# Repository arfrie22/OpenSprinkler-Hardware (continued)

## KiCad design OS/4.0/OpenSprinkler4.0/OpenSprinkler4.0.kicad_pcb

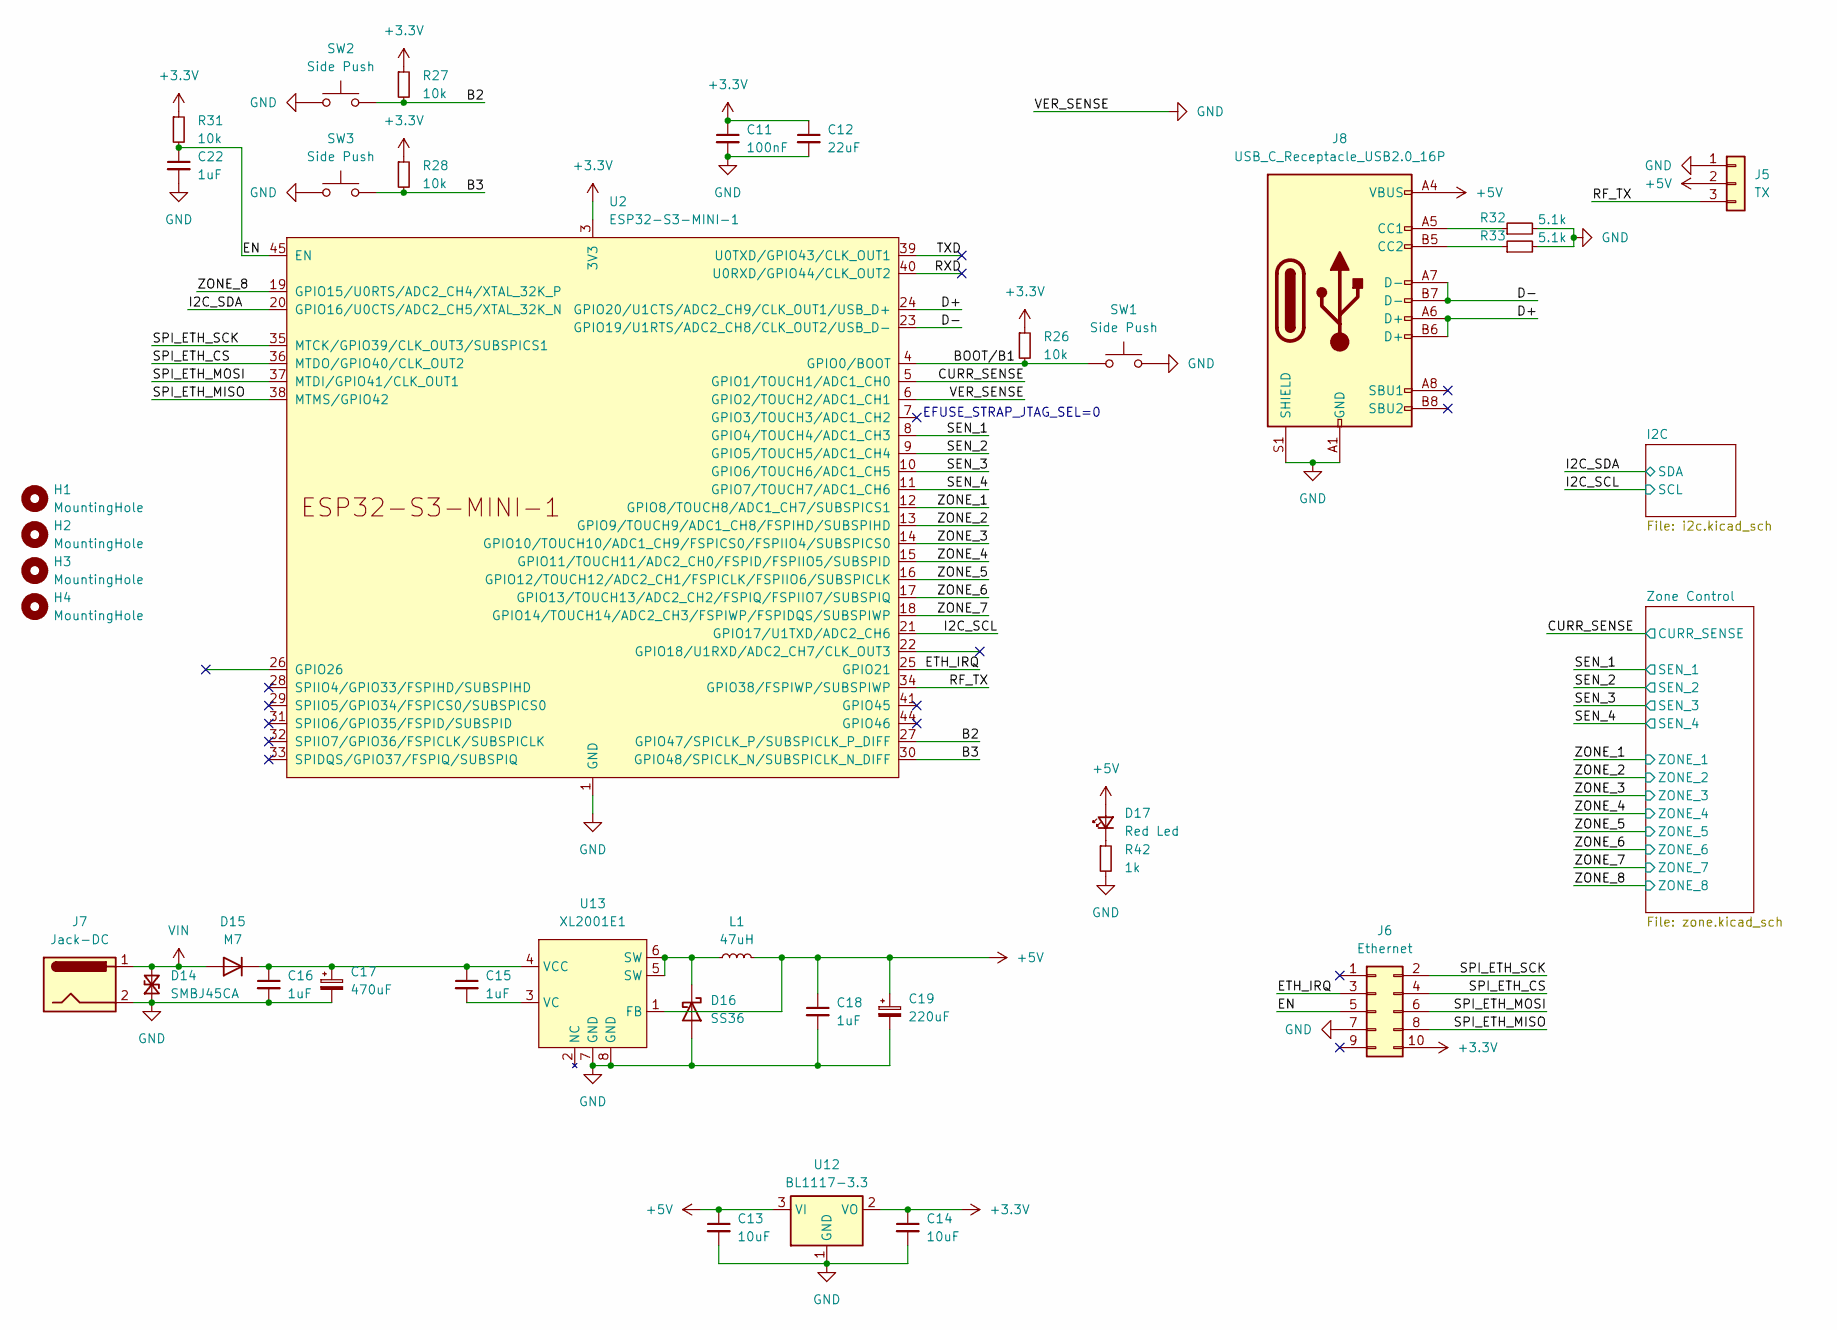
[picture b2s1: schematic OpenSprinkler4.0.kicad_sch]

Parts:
C11: 100nF; C_0603_1608Metric_Pad1.08x0.95mm_HandSolder; JLCPCB Part # C14663
C12: 22uF; C_0805_2012Metric_Pad1.18x1.45mm_HandSolder; JLCPCB Part # C45783
C13, C14: 10uF; C_0603_1608Metric_Pad1.08x0.95mm_HandSolder; JLCPCB Part # C96446
C15, C16, C18, C22: 1uF; C_0603_1608Metric_Pad1.08x0.95mm_HandSolder; JLCPCB Part # C15849
C17: 470uF; CP_Radial_L20.0mm_D10.0mm_P5.00mm_Horizontal; JLCPCB Part # C2760863
C19: 220uF; CP_Radial_L12.0mm_D8.0mm_P3.50mm_Horizontal; JLCPCB Part # C2831783
D14: SMBJ45CA; D_SMB; JLCPCB Part # C7466424
D15: M7; D_SMA; JLCPCB Part # C7420350
D16: SS36; D_SMA; JLCPCB Part # C7420367
D17: Red Led; LED_0603_1608Metric_Pad1.05x0.95mm_HandSolder; JLCPCB Part # C2286
H1, H2, H3, H4: MountingHole; MountingHole_5.6mm; JLCPCB Part # N/A
J5: TX; PinSocket_1x03_P2.54mm_Horizontal; Part Number 1-0301FBV0T; JLCPCB Part # C2935993
J6: Ethernet; IDC-Header_2x05_P2.54mm_Horizontal; JLCPCB Part # C9140
J7: Jack-DC; BarrelJack_Horizontal; JLCPCB Part # C3010533
J8: USB_C_Receptacle_USB2.0_16P; USB_C_Receptacle_HRO_TYPE-C-31-M-12; JLCPCB Part # C2927038
L1: 47uH; L_Sunlord_MWSA1004S; JLCPCB Part # C182153
R26, R27, R28, R31: 10k; R_0603_1608Metric_Pad0.98x0.95mm_HandSolder; JLCPCB Part # C25804
R32, R33: 5.1k; R_0603_1608Metric_Pad0.98x0.95mm_HandSolder; JLCPCB Part # C23186
R42: 1k; R_0603_1608Metric_Pad0.98x0.95mm_HandSolder; JLCPCB Part # C21190
SW1, SW2, SW3: Side Push; SW_Tactile_SPST_Angled_PTS645Vx83-2LFS; JLCPCB Part # C493059
U2: ESP32-S3-MINI-1; JLCPCB Part # C2913206
U12: BL1117-3.3; SOT-223-3_TabPin2; JLCPCB Part # C5400
U13: XL2001E1; SOP-8_3.9x4.9mm_P1.27mm; JLCPCB Part # C73336

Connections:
+3.3V: C11.1, C12.1, C14.1, J6.10, R26.1, R27.1, R28.1, R31.1, U2.3 (3V3), U12.2 (VO); also elsewhere on the board
+5V: C13.1, C18.1, C19.1, D17.2 (A), J5.2, J8.A4 (VBUS), J8.A9 (VBUS), J8.B4 (VBUS), J8.B9 (VBUS), L1.2, U12.3 (VI), U13.1 (FB); also elsewhere on the board
/B2: R27.2, SW2.1, U2.27 (GPIO47/SPICLK_P/SUBSPICLK_P_DIFF)
/B3: R28.2, SW3.1, U2.30 (GPIO48/SPICLK_N/SUBSPICLK_N_DIFF)
/BOOT/B1: R26.2, SW1.1, U2.4 (GPIO0/BOOT)
/CURR_SENSE: U2.5 (GPIO1/TOUCH1/ADC1_CH0); also elsewhere on the board
/D+: J8.A6 (D+), J8.B6 (D+), U2.24 (GPIO20/U1CTS/ADC2_CH9/CLK_OUT1/USB_D+)
/D-: J8.A7 (D-), J8.B7 (D-), U2.23 (GPIO19/U1RTS/ADC2_CH8/CLK_OUT2/USB_D-)
/EN: C22.1, J6.5, R31.2, U2.45 (EN)
/ETH_IRQ: J6.3, U2.25 (GPIO21)
/I2C_SCL: U2.21 (GPIO17/U1TXD/ADC2_CH6); also elsewhere on the board
/I2C_SDA: U2.20 (GPIO16/U0CTS/ADC2_CH5/XTAL_32K_N); also elsewhere on the board
/RF_TX: J5.3, U2.34 (GPIO38/FSPIWP/SUBSPIWP)
/RXD: U2.40 (U0RXD/GPIO44/CLK_OUT2)
/SEN_1: U2.8 (GPIO4/TOUCH4/ADC1_CH3); also elsewhere on the board
/SEN_2: U2.9 (GPIO5/TOUCH5/ADC1_CH4); also elsewhere on the board
/SEN_3: U2.10 (GPIO6/TOUCH6/ADC1_CH5); also elsewhere on the board
/SEN_4: U2.11 (GPIO7/TOUCH7/ADC1_CH6); also elsewhere on the board
/SPI_ETH_CS: J6.4, U2.36 (MTDO/GPIO40/CLK_OUT2)
/SPI_ETH_MISO: J6.8, U2.38 (MTMS/GPIO42)
/SPI_ETH_MOSI: J6.6, U2.37 (MTDI/GPIO41/CLK_OUT1)
/SPI_ETH_SCK: J6.2, U2.35 (MTCK/GPIO39/CLK_OUT3/SUBSPICS1)
/TXD: U2.39 (U0TXD/GPIO43/CLK_OUT1)
/ZONE_1: U2.12 (GPIO8/TOUCH8/ADC1_CH7/SUBSPICS1); also elsewhere on the board
/ZONE_2: U2.13 (GPIO9/TOUCH9/ADC1_CH8/FSPIHD/SUBSPIHD); also elsewhere on the board
/ZONE_3: U2.14 (GPIO10/TOUCH10/ADC1_CH9/FSPICS0/FSPIIO4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); also elsewhere on the board
/ZONE_4: U2.15 (GPIO11/TOUCH11/ADC2_CH0/FSPID/FSPIIO5/S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); also elsewhere on the board
/ZONE_5: U2.16 (GPIO12/TOUCH12/ADC2_CH1/FSPICLK/FSPIIO6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); also elsewhere on the board
/ZONE_6: U2.17 (GPIO13/TOUCH13/ADC2_CH2/FSPIQ/FSPIIO7/S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); also elsewhere on the board
/ZONE_7: U2.18 (GPIO14/TOUCH14/ADC2_CH3/FSPIWP/FSPIDQS/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); also elsewhere on the board
/ZONE_8: U2.19 (GPIO15/U0RTS/ADC2_CH4/XTAL_32K_P); also elsewhere on the board
GND: C11.2, C12.2, C13.2, C14.2, C16.2, C17.2, C18.2, C19.2, C22.2, D14.1 (A1), D16.2 (A), J5.1, J6.7, J7.2, J8.A1 (GND), J8.A12 (GND), J8.B1 (GND), J8.B12 (GND), J8.S1 (SHIELD), R32.2, R33.2, R42.2, SW1.2, SW2.2, SW3.2, U2.1 (GND), U2.2 (GND), U2.6 (GPIO2/TOUCH2/ADC1_CH1), U2.42 (GND), U2.43 (GND), U2.46 (GND), U2.47 (GND), U2.48 (GND), U2.49 (GND), U2.50 (GND), U2.51 (GND), U2.52 (GND), U2.53 (GND), U2.54 (GND), U2.55 (GND), U2.56 (GND), U2.57 (GND), U2.58 (GND), U2.59 (GND), U2.60 (GND), U2.61 (GND), U2.62 (GND), U2.63 (GND), U2.64 (GND), U2.65 (GND), U12.1 (GND), U13.7 (GND), U13.8 (GND); also elsewhere on the board
unnamed: C15.1, C16.1, C17.1, D15.1 (K), U13.4 (VCC)
unnamed: D16.1 (K), L1.1, U13.5 (SW), U13.6 (SW)
unnamed: D17.1 (K), R42.1
unnamed: J8.A5 (CC1), R32.1
unnamed: J8.B5 (CC2), R33.1
unnamed: C15.2, U13.3 (VC)
VIN: D14.2 (A2), D15.2 (A), J7.1; also elsewhere on the board

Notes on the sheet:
EFUSE_STRAP_JTAG_SEL=0

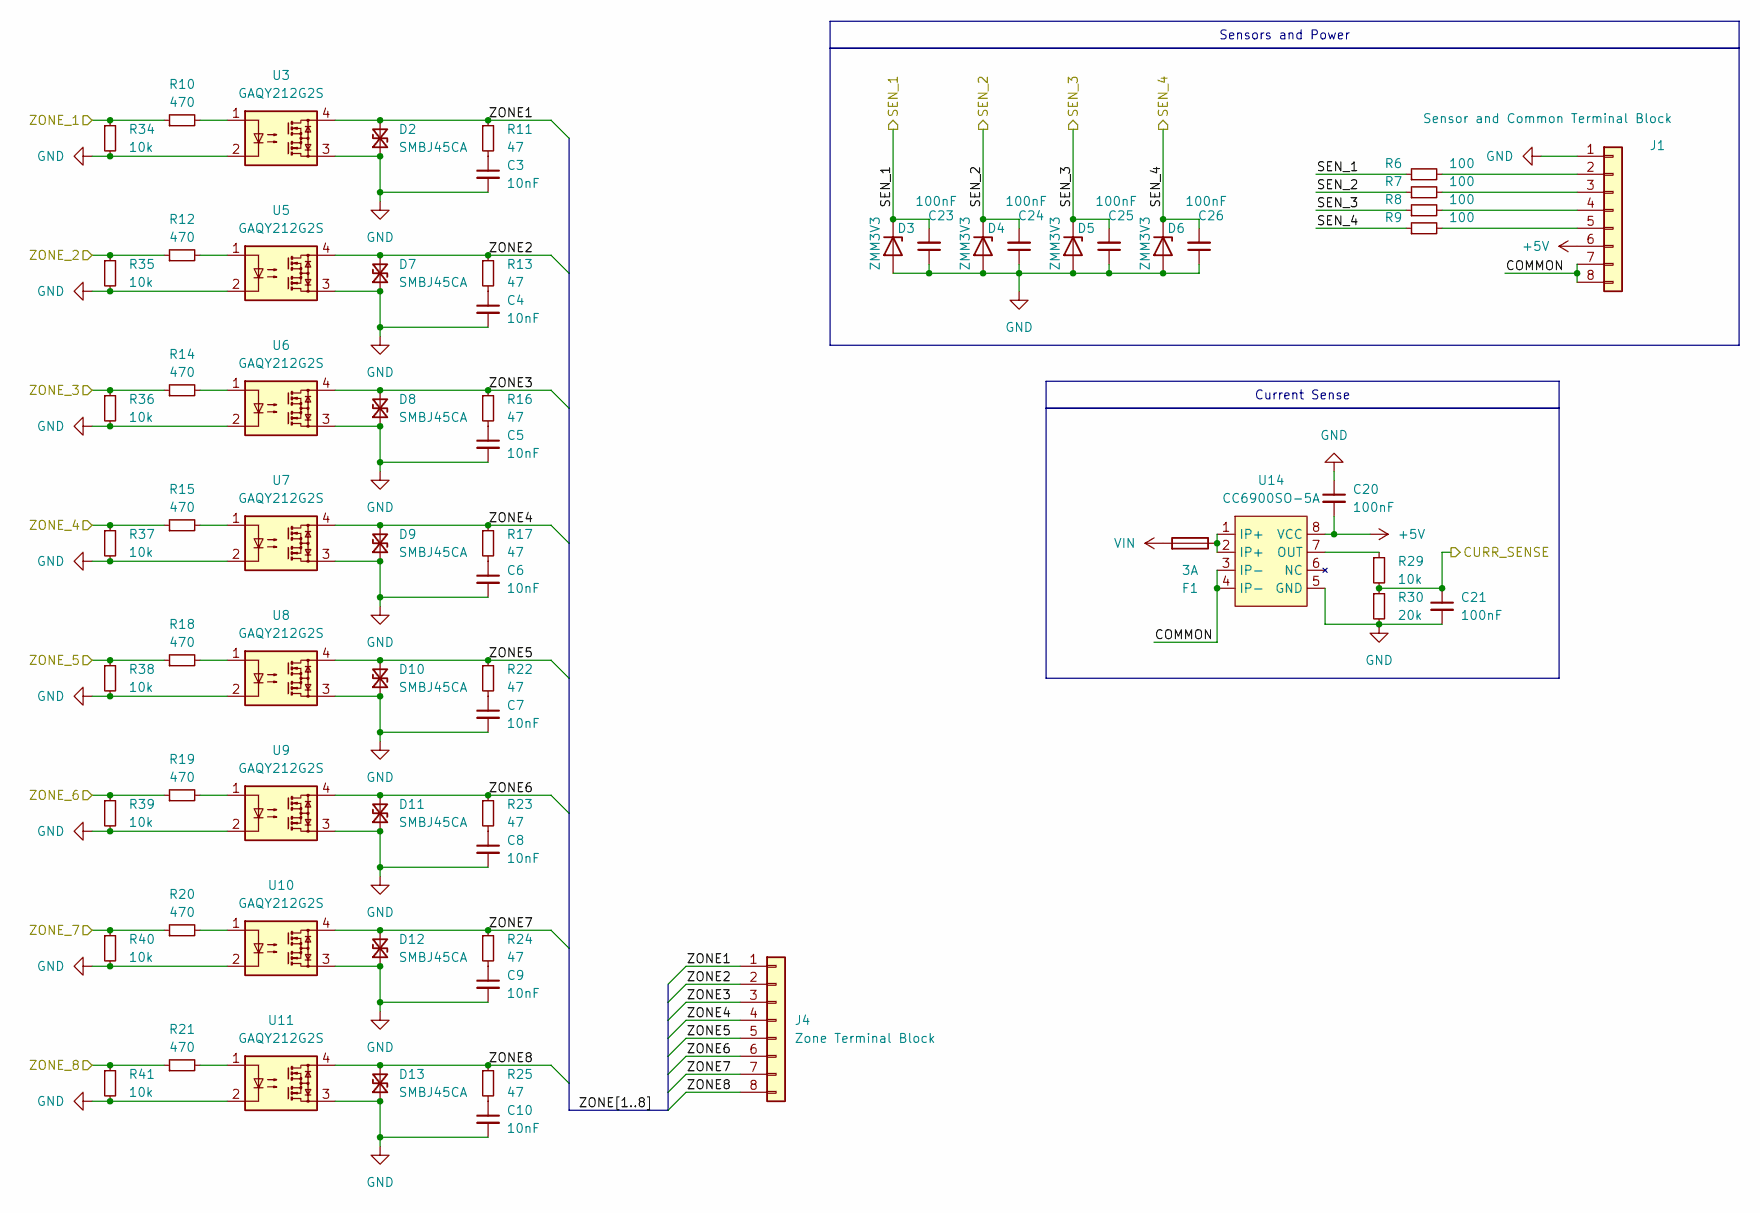
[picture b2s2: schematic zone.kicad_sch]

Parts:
C3, C4, C5, C6, C7, C8, C9, C10: 10nF; C_0603_1608Metric_Pad1.08x0.95mm_HandSolder; JLCPCB Part # C57112
C20, C21: 100nF; C_0603_1608Metric_Pad1.08x0.95mm_HandSolder; JLCPCB Part # C14663
C23, C24, C25, C26: 100nF; C_0603_1608Metric_Pad1.08x0.95mm_HandSolder
D2, D7, D8, D9, D10, D11, D12, D13: SMBJ45CA; D_SMB; JLCPCB Part # C7466424
D3, D4, D5, D6: ZMM3V3; D_MiniMELF; JLCPCB Part # C7497475
F1: 3A; Xucheng_Elec_5x20; JLCPCB Part # C3130
J1: Sensor and Common Terminal Block; Samtec_HPM-08-05-x-S_Straight_1x08_Pitch5.08mm; JLCPCB Part # C31423
J4: Zone Terminal Block; Samtec_HPM-08-05-x-S_Straight_1x08_Pitch5.08mm; JLCPCB Part # C31423
R6, R7, R8, R9: 100; R_0603_1608Metric_Pad0.98x0.95mm_HandSolder; JLCPCB Part # C22775
R10, R12, R14, R15, R18, R19, R20, R21: 470; R_0603_1608Metric_Pad0.98x0.95mm_HandSolder; JLCPCB Part # C23179
R11, R13, R16, R17, R22, R23, R24, R25: 47; R_0603_1608Metric_Pad0.98x0.95mm_HandSolder; JLCPCB Part # C23182
R29, R34, R35, R36, R37, R38, R39, R40, R41: 10k; R_0603_1608Metric_Pad0.98x0.95mm_HandSolder; JLCPCB Part # C25804
R30: 20k; R_0603_1608Metric_Pad0.98x0.95mm_HandSolder; JLCPCB Part # C4184
U3, U5, U6, U7, U8, U9, U10, U11: GAQY212G2S; SOP-4_3.8x4.1mm_P2.54mm; JLCPCB Part # C7435109
U14: CC6900SO-5A; SOP-8_3.9x4.9mm_P1.27mm; JLCPCB Part # C350864

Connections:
+5V: C20.2, J1.6, U14.8 (VCC); also elsewhere on the board
/CURR_SENSE: C21.1, R29.2, R30.1; also elsewhere on the board
/SEN_1: C23.2, D3.1 (K), R6.1; also elsewhere on the board
/SEN_2: C24.2, D4.1 (K), R7.1; also elsewhere on the board
/SEN_3: C25.2, D5.1 (K), R8.1; also elsewhere on the board
/SEN_4: C26.2, D6.1 (K), R9.1; also elsewhere on the board
/ZONE_1: R10.1, R34.1; also elsewhere on the board
/ZONE_2: R12.1, R35.1; also elsewhere on the board
/ZONE_3: R14.1, R36.1; also elsewhere on the board
/ZONE_4: R15.1, R37.1; also elsewhere on the board
/ZONE_5: R18.1, R38.1; also elsewhere on the board
/ZONE_6: R19.1, R39.1; also elsewhere on the board
/ZONE_7: R20.1, R40.1; also elsewhere on the board
/ZONE_8: R21.1, R41.1; also elsewhere on the board
/Zone Control/COMMON: J1.7, J1.8, U14.3 (IP-), U14.4 (IP-)
/Zone Control/ZONE1: D2.2 (A2), J4.1, R11.1, U3.4
/Zone Control/ZONE2: D7.2 (A2), J4.2, R13.1, U5.4
/Zone Control/ZONE3: D8.2 (A2), J4.3, R16.1, U6.4
/Zone Control/ZONE4: D9.2 (A2), J4.4, R17.1, U7.4
/Zone Control/ZONE5: D10.2 (A2), J4.5, R22.1, U8.4
/Zone Control/ZONE6: D11.2 (A2), J4.6, R23.1, U9.4
/Zone Control/ZONE7: D12.2 (A2), J4.7, R24.1, U10.4
/Zone Control/ZONE8: D13.2 (A2), J4.8, R25.1, U11.4
GND: C3.2, C4.2, C5.2, C6.2, C7.2, C8.2, C9.2, C10.2, C20.1, C21.2, C23.1, C24.1, C25.1, C26.1, D2.1 (A1), D3.2 (A), D4.2 (A), D5.2 (A), D6.2 (A), D7.1 (A1), D8.1 (A1), D9.1 (A1), D10.1 (A1), D11.1 (A1), D12.1 (A1), D13.1 (A1), J1.1, R30.2, R34.2, R35.2, R36.2, R37.2, R38.2, R39.2, R40.2, R41.2, U3.2, U3.3, U5.2, U5.3, U6.2, U6.3, U7.2, U7.3, U8.2, U8.3, U9.2, U9.3, U10.2, U10.3, U11.2, U11.3, U14.5 (GND); also elsewhere on the board
unnamed: C3.1, R11.2
unnamed: C4.1, R13.2
unnamed: C5.1, R16.2
unnamed: C6.1, R17.2
unnamed: C7.1, R22.2
unnamed: C8.1, R23.2
unnamed: C9.1, R24.2
unnamed: C10.1, R25.2
unnamed: F1.1, U14.1 (IP+), U14.2 (IP+)
unnamed: J1.2, R6.2
unnamed: J1.3, R7.2
unnamed: J1.4, R8.2
unnamed: J1.5, R9.2
unnamed: R10.2, U3.1
unnamed: R12.2, U5.1
unnamed: R14.2, U6.1
unnamed: R15.2, U7.1
unnamed: R18.2, U8.1
unnamed: R19.2, U9.1
unnamed: R20.2, U10.1
unnamed: R21.2, U11.1
unnamed: R29.1, U14.7 (OUT)
VIN: F1.2; also elsewhere on the board

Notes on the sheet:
Sensors and Power
Current Sense

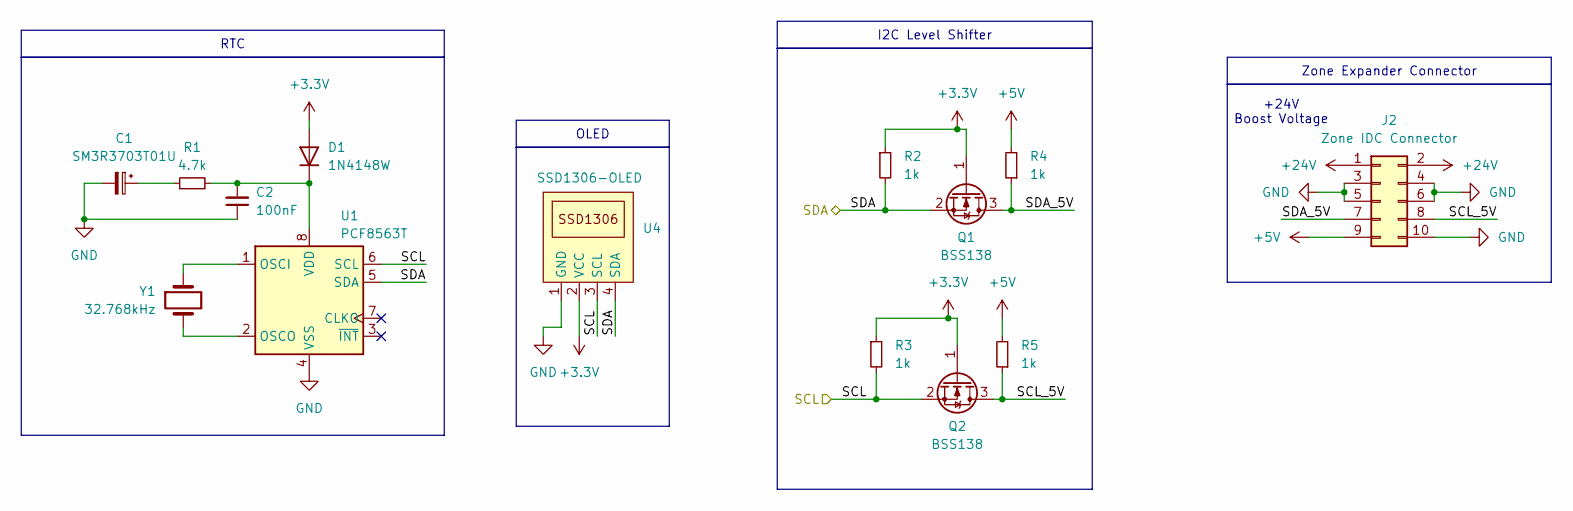
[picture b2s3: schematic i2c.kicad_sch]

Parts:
C1: SM3R3703T01U; SM3R3703T01; JLCPCB Part # C396469
C2: 100nF; C_0603_1608Metric_Pad1.08x0.95mm_HandSolder; JLCPCB Part # C14663
D1: 1N4148W; D_SOD-123; JLCPCB Part # C81598
J2: Zone IDC Connector; IDC-Header_2x05_P2.54mm_Horizontal; JLCPCB Part # C9140
Q1, Q2: BSS138; SOT-23; JLCPCB Part # C7420339
R1: 4.7k; R_0603_1608Metric_Pad0.98x0.95mm_HandSolder; JLCPCB Part # C23162
R2, R3, R4, R5: 1k; R_0603_1608Metric_Pad0.98x0.95mm_HandSolder; JLCPCB Part # C21190
U1: PCF8563T; SOIC-8_3.9x4.9mm_P1.27mm; JLCPCB Part # C7440
U4: SSD1306-OLED; JMD0.96D-1; JLCPCB Part # C2935975
Y1: 32.768kHz; Crystal_DS26_D2.0mm_L6.0mm_Horizontal; JLCPCB Part # C145163

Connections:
+3.3V: D1.2 (A), Q1.1 (G), Q2.1 (G), R2.1, R3.1, U4.2 (VCC); also elsewhere on the board
+5V: J2.9, R4.2, R5.2; also elsewhere on the board
+24V: J2.1, J2.2
/I2C/SCL_5V: J2.8, Q2.3 (D), R5.1
/I2C/SDA_5V: J2.7, Q1.3 (D), R4.1
/I2C_SCL: Q2.2 (S), R3.2, U1.6 (SCL), U4.3 (SCL); also elsewhere on the board
/I2C_SDA: Q1.2 (S), R2.2, U1.5 (SDA), U4.4 (SDA); also elsewhere on the board
GND: C1.2, C2.1, J2.3, J2.4, J2.5, J2.6, J2.10, U1.4 (VSS), U4.1 (GND); also elsewhere on the board
unnamed: C1.1, R1.1
unnamed: C2.2, D1.1 (K), R1.2, U1.8 (VDD)
unnamed: U1.1 (OSCI), Y1.1
unnamed: U1.2 (OSCO), Y1.2

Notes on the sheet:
OLED
Zone Expander Connector
I2C Level Shifter
RTC
+24V Boost Voltage

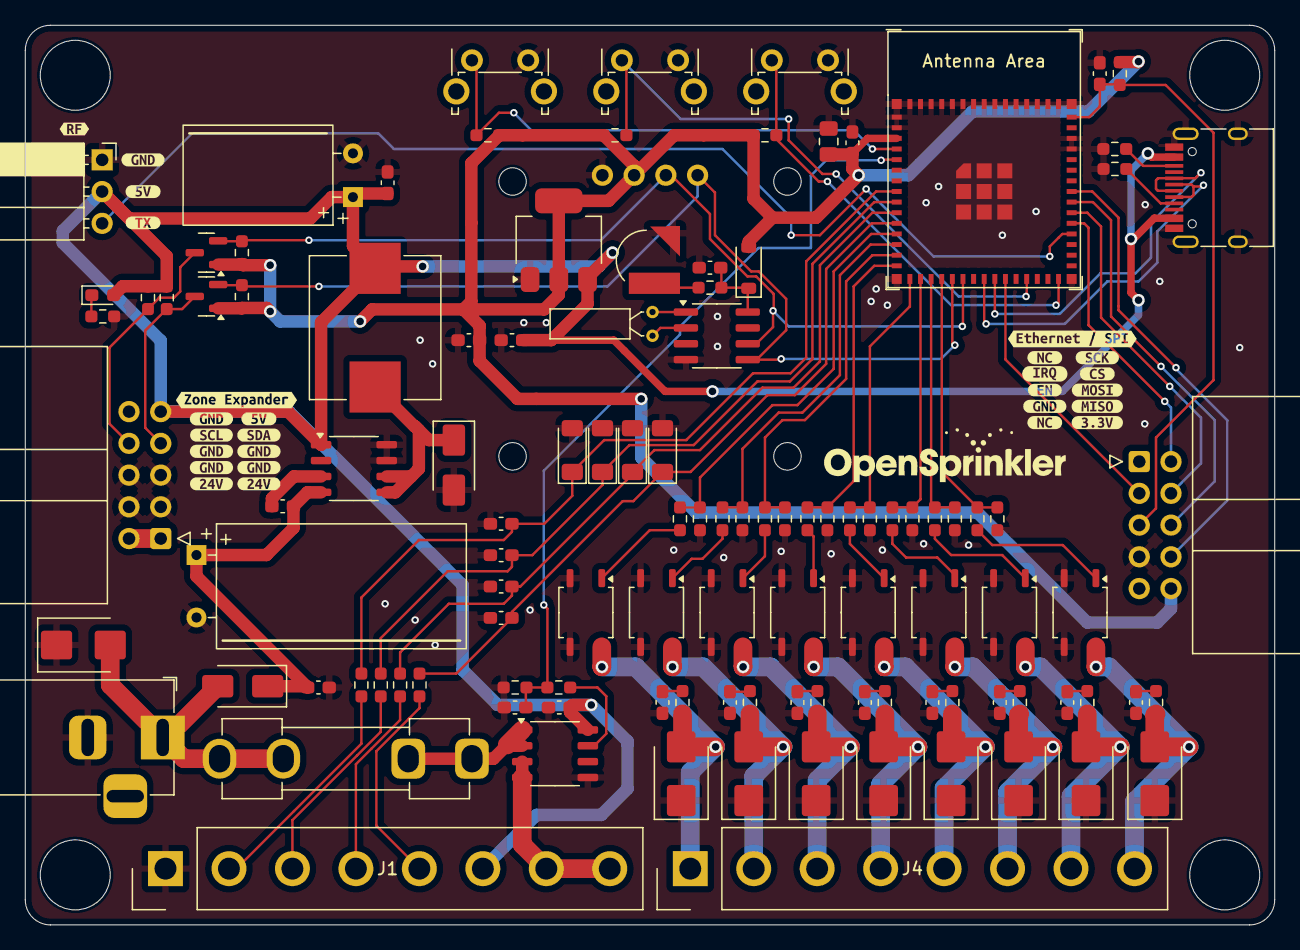
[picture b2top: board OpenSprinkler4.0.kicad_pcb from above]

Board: 2 copper layers, 100.0 x 72.0 mm, 144 parts (0 on the bottom side), 75 nets.

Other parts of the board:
kibuzzard-66A7F7F7: G***; kibuzzard-66A7F7F7
kibuzzard-66A7F74C: G***; kibuzzard-66A7F74C
kibuzzard-66A7F75B: G***; kibuzzard-66A7F75B
kibuzzard-66A7F829: G***; kibuzzard-66A7F829
kibuzzard-66A7FD7B: G***; kibuzzard-66A7FD7B
kibuzzard-66A7FD8D: G***; kibuzzard-66A7FD8D
kibuzzard-66A7FD67: G***; kibuzzard-66A7FD67
kibuzzard-66A7FD96: G***; kibuzzard-66A7FD96
kibuzzard-66A7FDEE: G***; kibuzzard-66A7FDEE
kibuzzard-66A7FE28: G***; kibuzzard-66A7FE28
kibuzzard-66A917B8: G***; kibuzzard-66A917B8
kibuzzard-66A950A2: G***; kibuzzard-66A950A2
kibuzzard-66A950A5: G***; kibuzzard-66A950A5
kibuzzard-66A950AB: G***; kibuzzard-66A950AB
kibuzzard-66A9503B: G***; kibuzzard-66A9503B
kibuzzard-66A9503E: G***; kibuzzard-66A9503E
kibuzzard-66A9508D: G***; kibuzzard-66A9508D
kibuzzard-66A9509C: G***; kibuzzard-66A9509C
kibuzzard-66A95035: G***; kibuzzard-66A95035
kibuzzard-66A95039: G***; kibuzzard-66A95039
kibuzzard-66A95040: G***; kibuzzard-66A95040
kibuzzard-66A95080: G***; kibuzzard-66A95080
kibuzzard-66A95085: G***; kibuzzard-66A95085
kibuzzard-66A95089: G***; kibuzzard-66A95089
kibuzzard-66A95092: G***; kibuzzard-66A95092
kibuzzard-66A95097: G***; kibuzzard-66A95097

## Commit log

2024-08-12 opensprinkler 4.0
2025-09-04 new design
